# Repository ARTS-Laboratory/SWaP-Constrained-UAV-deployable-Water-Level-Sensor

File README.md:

# SWaP-Constrained UAV-deployable Water-Level Sensor (SCUWLS)
UAV Deployable Stage Height Sensor with Magnetic Docking Mechanism

This work is dicussed in two papers:
1. Md Asifuzzaman Khan, Muhammad Usman Khan, Amanda Sarka, P. G. Tien Tran, Michelle Eigbe, Austin R. J. Downey, Jason D. Bakos, Erick Blasche, and Jasim Imran. Energy budget analysis of swap-constrained uav-deployable water-level sensors with varying sampling intervals and idle currents. In SPIE Defense + Commercial Sensing 2026. SPIE, 2026
2. Corinne Smith, Joud Satme, Jacob Martin, Austin R.J. Downey, Nikolaos Vitzilaios, and Jasim Imran. UAV rapidly-deployable stage sensor with electro-permanent magnet docking mechanism for flood monitoring in undersampled watersheds. HardwareX, 12:e00325, oct 2022. doi:10.1016/j.ohx.2022.e00325.

## Hardware

<p align="center">
Figure 1: The "Georgetown Version 0.5" of the sensor, showing  (a) the assembled sensor package, and (b) a cross-section view of the sensor.
</p>

<p align="center">
Figure 2: Sensors deployed for continuous monitoring in the Charleston, SC area.
</p>

<p align="center">
Figure 3: Drone delivering a sensor package underneath a structure using Electro Parmanent Magnet docking mechanism.
</p>

## Versions 

### V0
1. Data logging saved onto SD card
2. Battery monitoring
3. Solar load sharing
4. Measures stage, temperature, pressure, humidity
5. EPM with wireless toggling to attach under structures

### V1 (projected)
1. Adaptive sampling algorithm
2. Wireless data transfer with GUI
3. Camera integration

## Licensing and Citation

[![CC BY-SA 4.0][cc-by-sa-shield]][cc-by-sa]

This work is licensed under a
[Creative Commons Attribution-ShareAlike 4.0 International License][cc-by-sa].

[cc-by-sa]: http://creativecommons.org/licenses/by-sa/4.0/
[cc-by-sa-image]: https://licensebuttons.net/l/by-sa/4.0/88x31.png
[cc-by-sa-shield]: https://img.shields.io/badge/License-CC%20BY--SA%204.0-lightgrey.svg

Cite as:

@Misc{ARTSLabUavDeployableStage,     
  author = {{ARTS-L}ab},  
  howpublished = {GitHub},  
  title  = {{SWaP-Constrained UAV-deployable Water-Level Sensor} (SCUWLS)},    
  groups = {{ARTS-L}ab},    
  url    = {https://github.com/ARTS-Laboratory/SWaP-Constrained-UAV-deployable-Water-Level-Sensor},   
}

<br>

<p align="center">
https://github.com/ARTS-Laboratory/UAV-Deployable-Stage-Height-Sensor
</p>

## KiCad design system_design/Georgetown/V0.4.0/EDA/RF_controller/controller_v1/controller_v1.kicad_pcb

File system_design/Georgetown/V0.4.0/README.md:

# UAV Rapidly-Deployable Stage Sensor with Electro-permanent Magnet Docking Mechanism for Flood Monitoring in Undersampled Watersheds

## bill of materials
A complete bill of materials, with specifications for the base package, solar add-on module, and EPM add-on module

## CAD
STL and F3D files of 3D printed parts 

## code
Calibration and data collection codes

## EDA
KiCAD schematics and PCB layouts of main and daughter boards

## figures
SVG and PDF files of all figures presented in the work

## testing_data
Data from benchtop and field tests

## data_headers.csv
Example data headers for csv file generated by data_collection.ino

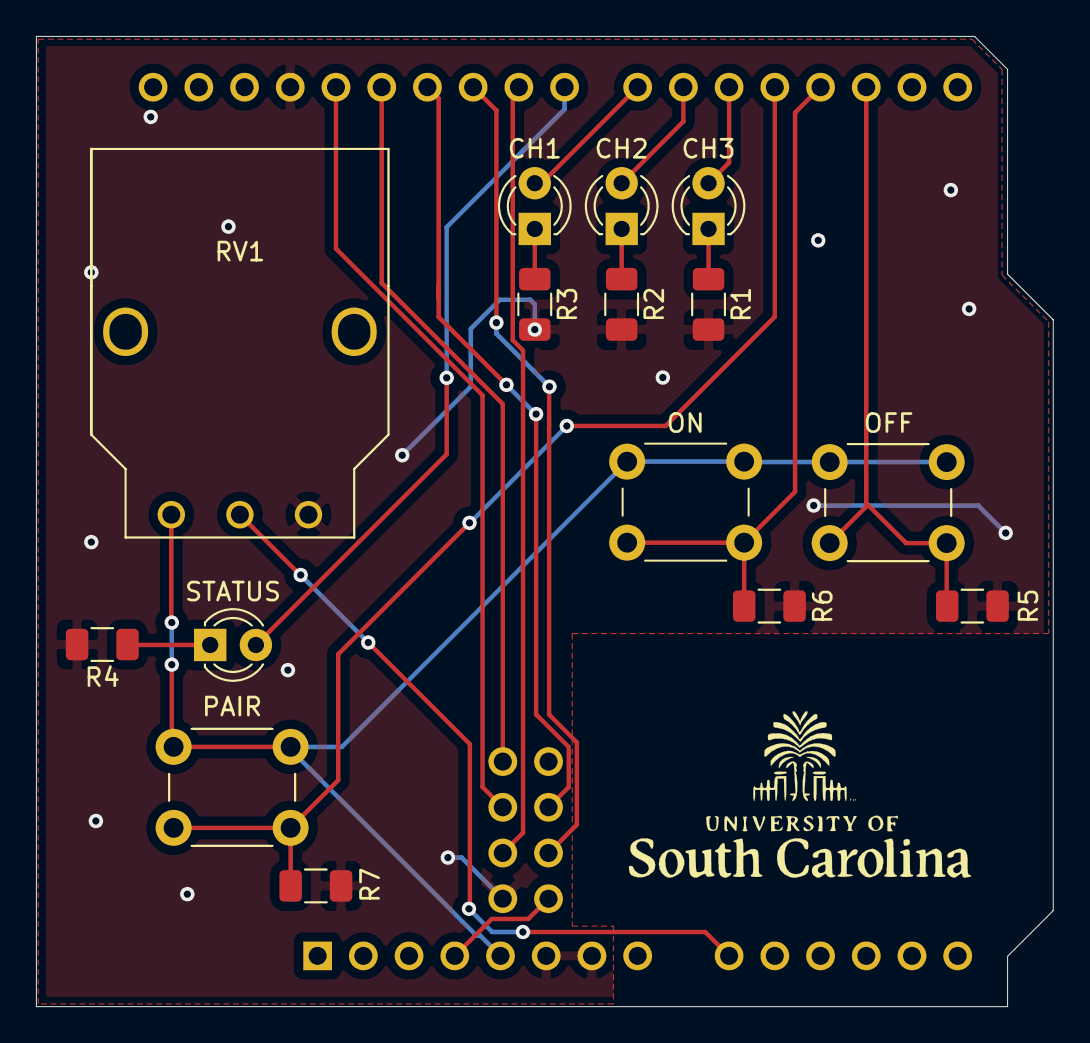
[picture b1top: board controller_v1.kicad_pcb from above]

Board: 2 copper layers, 56.5 x 53.9 mm, 17 parts (1 on the bottom side), 20 nets.

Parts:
A1: Arduino_UNO_R3
CH1, CH2, CH3: LED; LED_D3.0mm
OFF: SW_Push; SW_PUSH_6mm
ON: SW_Push; SW_PUSH_6mm
PAIR: SW_Push; SW_PUSH_6mm
R1, R2, R3, R4, R5, R6, R7: R; R_1206_3216Metric
RV1: R_POT; Bourns_PDB12
STATUS: LED; LED_D3.0mm
nRF24L01+: nRF24L01+

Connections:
GND: A1.6, A1.7, A1.29, R1.2, R2.2, R3.2, R4.2, R5.1, R6.2, R7.2, RV1.3, nRF24L01+.5
unnamed: A1.4, nRF24L01+.1
unnamed: A1.5, OFF.1, ON.1, PAIR.1, RV1.1
unnamed: A1.9, RV1.2
unnamed: A1.17, OFF.2, R5.2
unnamed: A1.18, ON.2, R6.1
unnamed: A1.19, PAIR.2, R7.1
unnamed: A1.20, CH3.2
unnamed: A1.21, CH2.2
unnamed: A1.22, CH1.2
unnamed: A1.23, STATUS.2
unnamed: A1.24, nRF24L01+.6
unnamed: A1.25, nRF24L01+.2
unnamed: A1.26, nRF24L01+.3
unnamed: A1.27, nRF24L01+.8
unnamed: A1.28, nRF24L01+.7
unnamed: CH3.1, R1.1
unnamed: CH2.1, R2.1
unnamed: CH1.1, R3.1
unnamed: R4.1, STATUS.1

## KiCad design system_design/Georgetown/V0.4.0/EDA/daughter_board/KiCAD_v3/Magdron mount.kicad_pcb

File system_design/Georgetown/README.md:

# Gerogetown
UAV deployable sensor package for measuring water height. 

## V0.1
1. Oldest version
2. Basic datalogger setup with modular RTC and SD card
3. Accelerometer integrated into daughter board

## V0.2
1. Teensy 4.0 microcontroller
2. Added environmental sensor

## V0.3
1. Teensy 4.0 or Arduino Nano microcontroller
2. Added DC current sensor

## V0.4
1. Arduino Nano microcontroller
2. Magnet power control circuit on daughter board
3. No accelerometer on daughter board
4. Solar panel load sharing on daughter board

## V0.5
1. Arduino Nano microcontroller
2. Uses dynamic sleep interval depending on battery voltage level
3. Uses permanent magnet to attach to steel structures
4. Easy sliding water-proof clear tube

## V0.6 (Proposed)
### Power electronics upgrade from V0.5
1.  Back to being UAV deployable using [this system](https://github.com/ARTS-Laboratory/UAV-Understructure-Sensor-Deployment-and-Recovery-System).
2.  Uses [buck converter](https://www.mouser.com/ProductDetail/Texas-Instruments/TPSM84203EAB?qs=EU6FO9ffTwdvD6IyQBtt5A%3D%3D&mgh=1&utm_id=22370133501&utm_source=google&utm_medium=cpc&utm_marketing_tactic=amercorp&gad_source=1&gad_campaignid=22380187564&gbraid=0AAAAADn_wf2gWZzSurQARsbyVMmz_4UDQ&gclid=Cj0KCQjw4qHEBhCDARIsALYKFNO-ZgKxWQY3H1w5GanZ_Tstxw3fUVWm0au9QuEBnVr6LlNByRsZf7YaAo9nEALw_wcB) instead of linear voltage regulator
3. Uses module that has [single ultra sound transducer](https://cdn.shopify.com/s/files/1/0550/8091/0899/files/11832.pdf?v=1726578772) to lower current consumption.

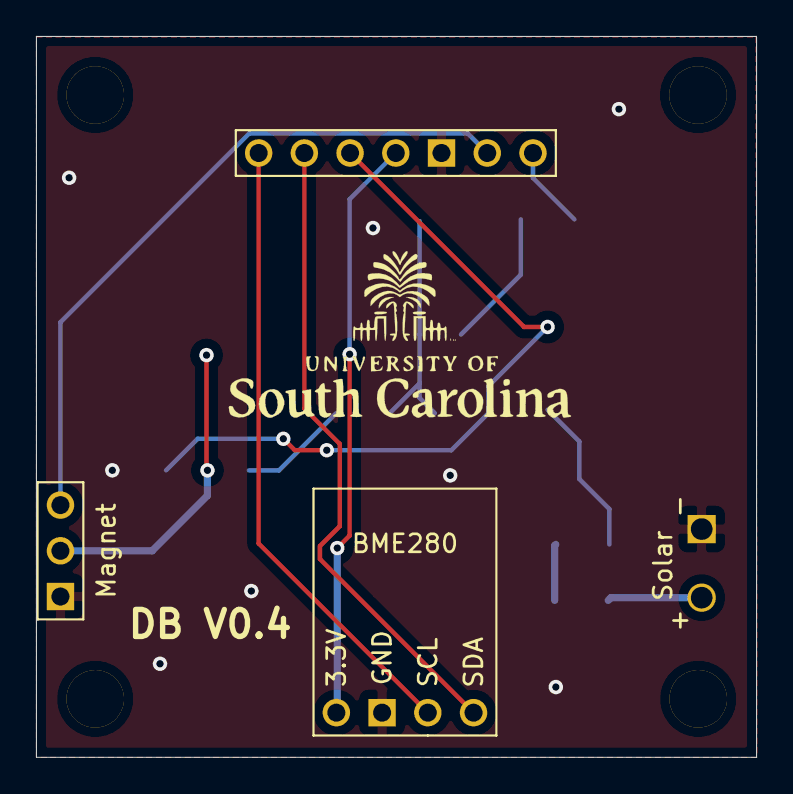
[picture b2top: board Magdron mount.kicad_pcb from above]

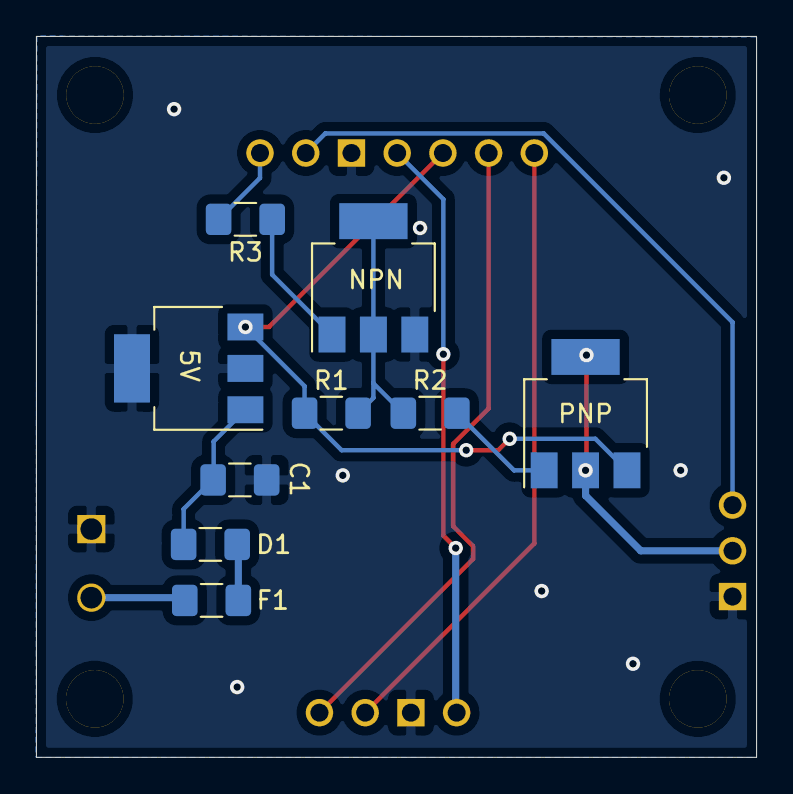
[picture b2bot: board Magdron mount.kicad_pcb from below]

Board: 2 copper layers, 40.0 x 40.0 mm, 18 parts (10 on the bottom side), 14 nets.

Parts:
5V: KA78M05_TO252; SOT-223-3_TabPin2
.: .; uofsc_logo_0_75in
.#2, .#3, .#4, .#5: MountingHole_3.2mm_M3_DIN965_Pad
BME280: BME280
C1: C; R_1206_3216Metric_Pad1.42x1.75mm_HandSolder
D1: D; R_1206_3216Metric_Pad1.42x1.75mm_HandSolder
F1: Fuse; R_1206_3216Metric_Pad1.42x1.75mm_HandSolder
Magnet: MAG-MAG; Magnet
NPN: BCP56; SOT-223-3_TabPin2
PNP: BCP51; SOT-223-3_TabPin2
R1: 1k; R_1206_3216Metric_Pad1.42x1.75mm_HandSolder
R2, R3: 100; R_1206_3216Metric_Pad1.42x1.75mm_HandSolder
Solar: power_input; XT60PW
U4: top_rail_v2

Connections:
GND: 5V.2, BME280.2, C1.1, Magnet.1, NPN.3, Solar.1, U4.6
unnamed: Magnet.2, PNP.2
unnamed: Magnet.3, U4.7
unnamed: 5V.1, C1.2, D1.1
unnamed: D1.2, F1.1
unnamed: F1.2, Solar.2
unnamed: PNP.1, R2.1
unnamed: 5V.3, PNP.3, R1.1, U4.4
unnamed: NPN.1, R3.1
unnamed: NPN.2, R1.2, R2.2
unnamed: R3.2, U4.8
unnamed: BME280.1, U4.5
unnamed: BME280.3, U4.2
unnamed: BME280.4, U4.3

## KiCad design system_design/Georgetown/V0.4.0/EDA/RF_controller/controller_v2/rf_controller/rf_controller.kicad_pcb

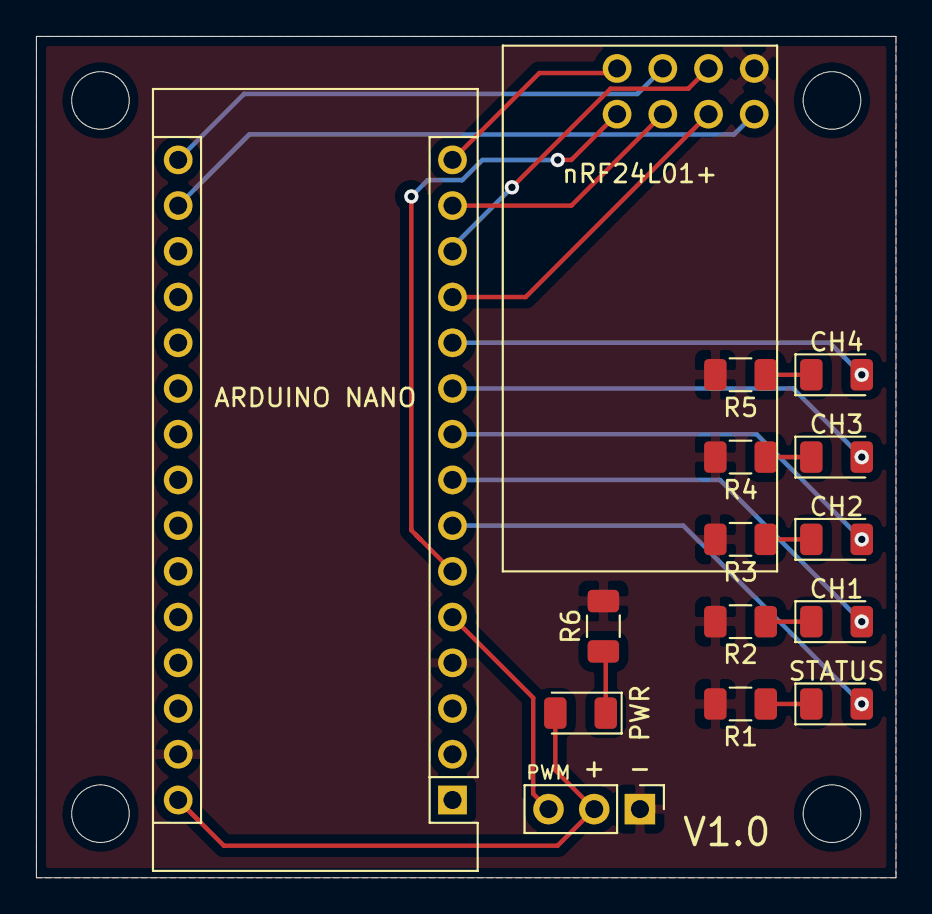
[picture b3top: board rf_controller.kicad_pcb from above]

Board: 2 copper layers, 47.8 x 46.7 mm, 15 parts (1 on the bottom side), 21 nets.

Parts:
ARDUINO NANO: Arduino_Nano_v2.x; Arduino_Nano
CH1, CH2, CH3, CH4: LED; LED_1206_3216Metric
PWM: Conn_01x03_Male; PinHeader_1x03_P2.54mm_Vertical
PWR: LED; LED_1206_3216Metric
R1, R2, R3, R4, R5, R6: R; R_1206_3216Metric
STATUS: LED; LED_1206_3216Metric
nRF24L01+: nRF24L01+

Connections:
GND: ARDUINO NANO.4, ARDUINO NANO.29, PWM.1, R1.2, R2.2, R3.2, R4.2, R5.2, R6.2, nRF24L01+.5
unnamed: ARDUINO NANO.5, PWM.3
unnamed: ARDUINO NANO.6, nRF24L01+.4
unnamed: ARDUINO NANO.7, STATUS.2
unnamed: ARDUINO NANO.8, CH1.2
unnamed: ARDUINO NANO.9, CH2.2
unnamed: ARDUINO NANO.10, CH3.2
unnamed: ARDUINO NANO.11, CH4.2
unnamed: ARDUINO NANO.12, nRF24L01+.2
unnamed: ARDUINO NANO.13, nRF24L01+.6
unnamed: ARDUINO NANO.14, nRF24L01+.3
unnamed: ARDUINO NANO.15, nRF24L01+.8
unnamed: ARDUINO NANO.16, nRF24L01+.7
unnamed: ARDUINO NANO.17, nRF24L01+.1
unnamed: ARDUINO NANO.30, PWM.2, PWR.2
unnamed: R1.1, STATUS.1
unnamed: CH1.1, R2.1
unnamed: CH2.1, R3.1
unnamed: CH3.1, R4.1
unnamed: CH4.1, R5.1
unnamed: PWR.1, R6.1

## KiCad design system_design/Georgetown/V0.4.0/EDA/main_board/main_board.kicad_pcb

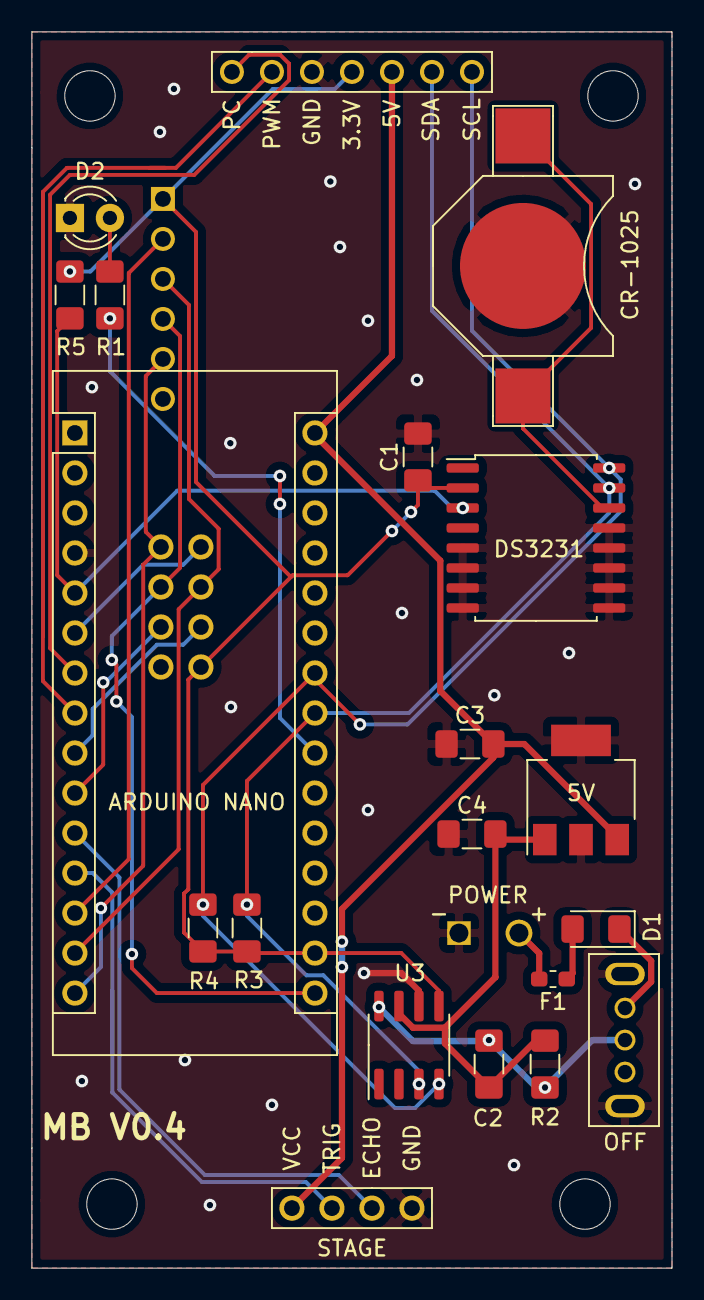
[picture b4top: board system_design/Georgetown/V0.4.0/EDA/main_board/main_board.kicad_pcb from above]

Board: 2 copper layers, 40.6 x 78.5 mm, 23 parts (0 on the bottom side), 25 nets.

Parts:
5V: KA78M05_TO252; SOT-223-3_TabPin2
ARDUINO NANO: Arduino_Nano_v2.x-MCU_Module; Arduino_Nano
C1, C2, C3, C4: C; C_1206_3216Metric_Pad1.42x1.75mm_HandSolder
CR-1025: Battery_Cell; battery_holder_10mm
D1: D; D_1206_3216Metric_Pad1.42x1.75mm_HandSolder
D2: LED; LED_D3.0mm
DS3231: DS3231M; SOIC-16W_7.5x10.3mm_P1.27mm
F1: Fuse; R_0603_1608Metric_Pad1.05x0.95mm_HandSolder
MICRO SD: small_microSD; small_microSD_v2
POWER: XP60PW; XT60PW
R1: 1k; C_1206_3216Metric_Pad1.42x1.75mm_HandSolder
R2: Rs; R_1206_3216Metric_Pad1.42x1.75mm_HandSolder
R3, R4: 4.7k; C_1206_3216Metric_Pad1.42x1.75mm_HandSolder
R5: 4.7k; R_1206_3216Metric_Pad1.42x1.75mm_HandSolder
STAGE: HCSR04
U1: top_rail_v2
U3: INA219AxD; SOIC-8_3.9x4.9mm_P1.27mm
nRF24L01+1: nRF24L01+
switch1: grounded_switch

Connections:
GND: 5V.2, ARDUINO NANO.4, ARDUINO NANO.29, C1.2, C3.1, C4.1, CR-1025.2, D2.1, DS3231.5, DS3231.6, DS3231.7, DS3231.8, DS3231.9, DS3231.10, DS3231.11, DS3231.12, DS3231.13, MICRO SD.6, POWER.1, STAGE.1, U1.6, U3.6, nRF24L01+1.5, switch1.4, switch1.5
unnamed: ARDUINO NANO.5, DS3231.3, R5.1
unnamed: ARDUINO NANO.6, nRF24L01+1.4
unnamed: ARDUINO NANO.7, U1.8
unnamed: ARDUINO NANO.8, U1.7
unnamed: ARDUINO NANO.9, nRF24L01+1.2
unnamed: ARDUINO NANO.10, nRF24L01+1.6
unnamed: ARDUINO NANO.11, STAGE.2
unnamed: ARDUINO NANO.12, STAGE.3
unnamed: ARDUINO NANO.13, MICRO SD.2
unnamed: ARDUINO NANO.14, MICRO SD.3, nRF24L01+1.3
unnamed: ARDUINO NANO.15, MICRO SD.5, nRF24L01+1.8
unnamed: ARDUINO NANO.16, MICRO SD.4, nRF24L01+1.7
unnamed: ARDUINO NANO.17, C1.1, DS3231.2, MICRO SD.1, R3.1, R4.1, R5.2, U1.5, U3.5, nRF24L01+1.1
unnamed: ARDUINO NANO.22, R1.1
unnamed: ARDUINO NANO.23, DS3231.15, R3.2, U1.3, U3.3
unnamed: ARDUINO NANO.24, DS3231.16, R4.2, U1.2, U3.4
unnamed: 5V.3, ARDUINO NANO.30, C3.2, STAGE.4, U1.4
unnamed: CR-1025.1, DS3231.14
unnamed: C2.1, R2.1, U3.8, switch1.2
unnamed: 5V.1, C2.2, C4.2, R2.2, U3.7
unnamed: D1.1, switch1.1
unnamed: D1.2, F1.1
unnamed: D2.2, R1.2
unnamed: F1.2, POWER.2

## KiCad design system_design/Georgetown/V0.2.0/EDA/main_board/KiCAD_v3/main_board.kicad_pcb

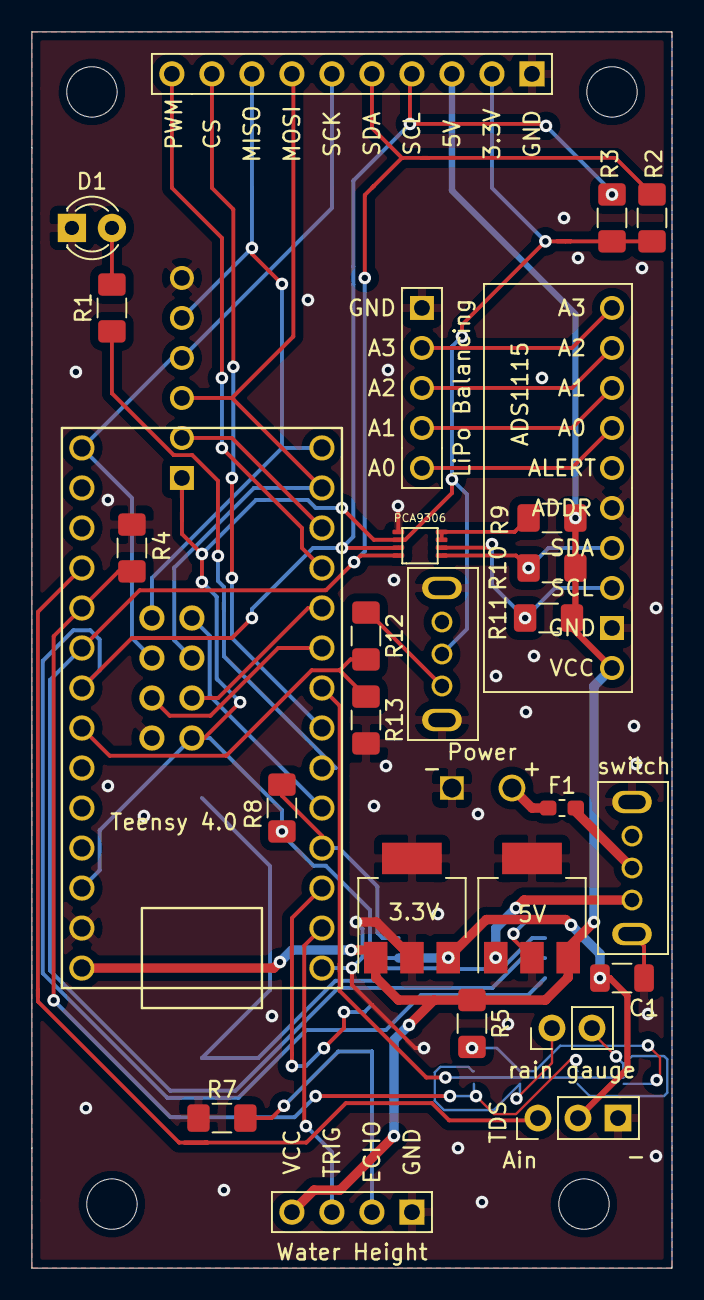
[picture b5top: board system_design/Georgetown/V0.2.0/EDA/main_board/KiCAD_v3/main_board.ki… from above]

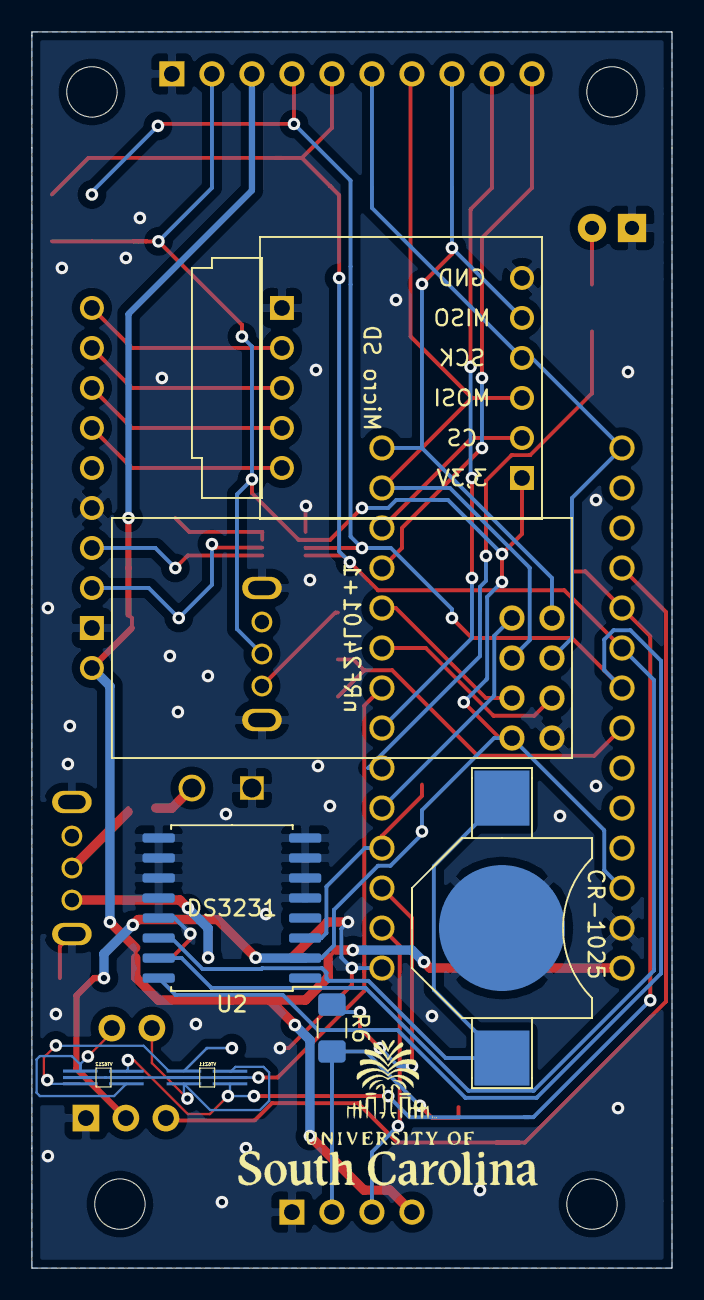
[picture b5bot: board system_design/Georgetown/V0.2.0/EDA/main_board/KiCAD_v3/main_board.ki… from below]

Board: 2 copper layers, 40.6 x 78.5 mm, 35 parts (3 on the bottom side), 39 nets.

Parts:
3.3V, 5V: KA78M05_TO252; SOT-223-3_TabPin2
ADS1115: ADS1115
C1: C; R_1206_3216Metric
CR-1025: Battery_Cell; battery_holder_10mm
D1: LED; LED_D3.0mm
F1: Fuse; R_0603_1608Metric_Pad1.05x0.95mm_HandSolder
LiPo Balancing: ADS_Conn
Micro SD: small_microSD
PCA9306: PCA9306
Power: XP60PW; XT60PW
R1, R12: 1k; R_1206_3216Metric_Pad1.42x1.75mm_HandSolder
R2, R3, R8, R10, R11: 4.7k; R_1206_3216Metric_Pad1.42x1.75mm_HandSolder
R4, R5: R; R_1206_3216Metric_Pad1.42x1.75mm_HandSolder
R6: 4.4k; R_1206_3216Metric_Pad1.42x1.75mm_HandSolder
R7: 4.1k; R_1206_3216Metric_Pad1.42x1.75mm_HandSolder
R9: 200; R_1206_3216Metric_Pad1.42x1.75mm_HandSolder
R13: 10k; R_1206_3216Metric_Pad1.42x1.75mm_HandSolder
TDS: tds_3pin; PinHeader_1x03_P2.54mm_Vertical
Teensy 4.0: Teensy4.0; teensy4.0
U2: DS3231M; SOIC-16W_7.5x10.3mm_P1.27mm
VT6Z11, VT6Z12: VT6Z1
Water Height: HCSR04
nRF24L01+1: nRF24L01+
rain gauge: rg_2pin; PinHeader_1x02_P2.54mm_Vertical
switch: grounded_switch
switch2: grounded_switch-whs5-rescue; grounded_switch
top_rail1: top_rail

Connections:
GND: 3.3V.2, 5V.2, ADS1115.6, ADS1115.9, C1.2, CR-1025.2, D1.1, LiPo Balancing.1, Micro SD.6, PCA9306.1, Power.1, R4.2, R7.1, R13.2, TDS.3, Teensy 4.0.1, Teensy 4.0.32, U2.5, U2.6, U2.7, U2.8, U2.9, U2.10, U2.11, U2.12, U2.13, Water Height.1, nRF24L01+1.5, switch.4, switch.5, switch2.4, switch2.5, top_rail1.9
unnamed: CR-1025.1, U2.14
unnamed: 3.3V.3, C1.1, Micro SD.1, PCA9306.2, R2.1, R3.1, R8.1, TDS.2, Teensy 4.0.31, U2.2, nRF24L01+1.1, switch2.2, top_rail1.8
unnamed: D1.2, R1.2
unnamed: F1.1, Power.2
unnamed: F1.2, switch.2
unnamed: Micro SD.2, Teensy 4.0.12
unnamed: Micro SD.3, Teensy 4.0.13, nRF24L01+1.3, top_rail1.3
unnamed: Micro SD.4, Teensy 4.0.20, nRF24L01+1.7, top_rail1.4
unnamed: Micro SD.5, Teensy 4.0.14, nRF24L01+1.8, top_rail1.2
unnamed: R1.1, Teensy 4.0.6
unnamed: PCA9306.4, R2.2, Teensy 4.0.25, U2.15, top_rail1.5
unnamed: PCA9306.3, R3.2, Teensy 4.0.26, U2.16, top_rail1.6
unnamed: R4.1, Teensy 4.0.24, VT6Z11.4, VT6Z12.6
unnamed: R5.2, VT6Z11.1, VT6Z12.3
unnamed: R6.1, Teensy 4.0.3
unnamed: R6.2, R7.2, Water Height.2
unnamed: R8.2, Teensy 4.0.4, U2.3
unnamed: PCA9306.7, PCA9306.8, R9.2
unnamed: ADS1115.7, PCA9306.5, R10.1
unnamed: 3.3V.1, 5V.3, ADS1115.10, R5.1, R9.1, R10.2, R11.2, Teensy 4.0.33, Water Height.4, top_rail1.7
unnamed: ADS1115.8, PCA9306.6, R11.1
unnamed: R12.1, switch2.1
unnamed: R12.2, R13.1, Teensy 4.0.27
unnamed: TDS.1, Teensy 4.0.23
unnamed: Teensy 4.0.2, Water Height.3
unnamed: Teensy 4.0.5, nRF24L01+1.4
unnamed: Teensy 4.0.7, top_rail1.1
unnamed: Teensy 4.0.8, VT6Z11.2, VT6Z11.5, VT6Z12.2, VT6Z12.5
unnamed: Teensy 4.0.9, nRF24L01+1.6
unnamed: Teensy 4.0.10, nRF24L01+1.2
unnamed: Teensy 4.0.11, top_rail1.10
unnamed: ADS1115.1, LiPo Balancing.2
unnamed: ADS1115.2, LiPo Balancing.3
unnamed: ADS1115.3, LiPo Balancing.4
unnamed: ADS1115.4, LiPo Balancing.5
unnamed: 5V.1, switch.1
unnamed: VT6Z11.3, VT6Z11.6, rain gauge.1
unnamed: VT6Z12.1, VT6Z12.4, rain gauge.2

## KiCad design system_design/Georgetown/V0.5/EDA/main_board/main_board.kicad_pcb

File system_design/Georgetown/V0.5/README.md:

# UAV Rapidly-Deployable Stage Sensor with Permanent Magnet Docking Mechanism for Flood Monitoring in Undersampled Watersheds
## Deployment note
* Do not plug or unplug the SD card while power is on. Swtich must be turned to the off position to plug/unplug the SD card. 
## Fully assembled sensor package

## V0.5 PCB Top side

## V0.5 PCB Bottom side

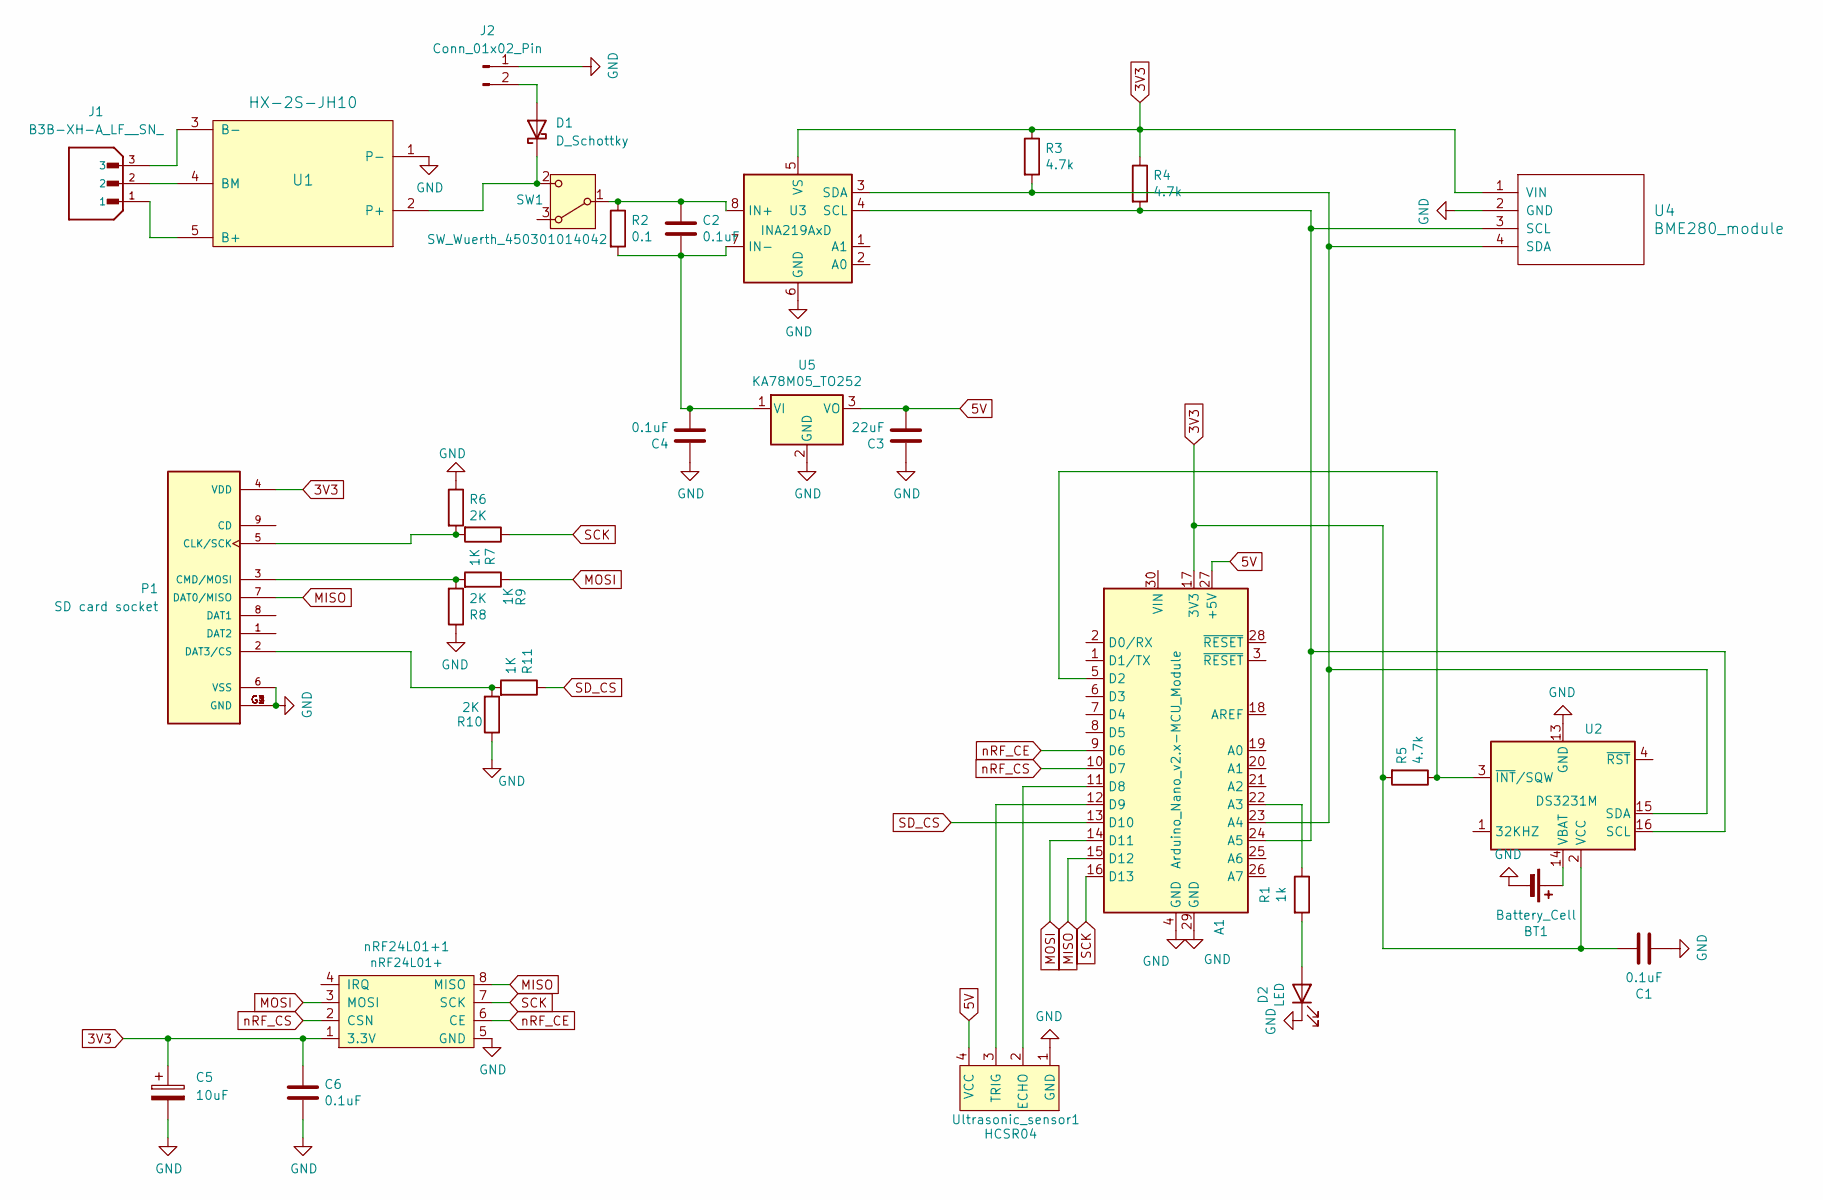
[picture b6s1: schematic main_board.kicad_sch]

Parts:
A1: Arduino_Nano_v2.x-MCU_Module; Arduino_Nano
BT1: Battery_Cell; battery_holder_10mm
C1, C2, C4: 0.1uF; C_1206_3216Metric_Pad1.42x1.75mm_HandSolder
C3: 22uF; C_1206_3216Metric_Pad1.42x1.75mm_HandSolder
C5: 10uF; CP_Radial_D4.0mm_P2.00mm
C6: 0.1uF; C_1206_3216Metric_Pad1.33x1.80mm_HandSolder
D1: D_Schottky; D_1206_3216Metric
D2: LED; LED_D3.0mm
J1: B3B-XH-A_LF__SN_; XH2.54; PARTREV 7/4/21
J2: Conn_01x02_Pin; PinHeader_1x02_P2.54mm_Vertical
P1: SD card socket; SUNTECH_ST-TF-003A
R1: 1k; C_1206_3216Metric_Pad1.42x1.75mm_HandSolder
R2: 0.1; R_1206_3216Metric_Pad1.42x1.75mm_HandSolder
R3, R4: 4.7k; C_1206_3216Metric_Pad1.42x1.75mm_HandSolder
R5: 4.7k; R_1206_3216Metric_Pad1.42x1.75mm_HandSolder
R6, R8, R10: 2K; C_1206_3216Metric_Pad1.33x1.80mm_HandSolder
R7, R9, R11: 1K; C_1206_3216Metric_Pad1.33x1.80mm_HandSolder
SW1: SW_Wuerth_450301014042; SW_Slide-03_Wuerth-WS-SLTV_10x2.5x6.4_P2.54mm
U1: HX-2S-JH10
U2: DS3231M; SOIC-16W_7.5x10.3mm_P1.27mm
U3: INA219AxD; SOIC-8_3.9x4.9mm_P1.27mm
U4: BME280_module
U5: KA78M05_TO252; SOT-223-3_TabPin2
Ultrasonic_sensor1: HCSR04
nRF24L01+1: nRF24L01+

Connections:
3V3: A1.17 (3V3), C1.1, C5.1, C6.1, P1.4 (VDD), R3.1, R4.1, R5.2, U2.2 (VCC), U3.5 (VS), U4.1 (VIN), nRF24L01+1.1 (3.3V)
5V: A1.27 (+5V), C3.2, U5.3 (VO), Ultrasonic_sensor1.4 (VCC)
GND: A1.4 (GND), A1.29 (GND), BT1.2 (-), C1.2, C3.1, C4.1, C5.2, C6.2, D2.1 (K), J2.1, P1.6 (VSS), P1.G1 (GND), P1.G2 (GND), P1.G3 (GND), P1.G4 (GND), R6.1, R8.1, R10.1, U1.1 (P-), U2.5 (GND), U2.6 (GND), U2.7 (GND), U2.8 (GND), U2.9 (GND), U2.10 (GND), U2.11 (GND), U2.12 (GND), U2.13 (GND), U3.6 (GND), U4.2 (GND), U5.2 (GND), Ultrasonic_sensor1.1 (GND), nRF24L01+1.5 (GND)
MISO: A1.15 (D12), P1.7 (DAT0/MISO), nRF24L01+1.8 (MISO)
MOSI: A1.14 (D11), R9.1, nRF24L01+1.3 (MOSI)
unnamed: A1.22 (A3), R1.1
unnamed: A1.23 (A4), R3.2, U2.15 (SDA), U3.3 (SDA), U4.4 (SDA)
unnamed: A1.24 (A5), R4.2, U2.16 (SCL), U3.4 (SCL), U4.3 (SCL)
unnamed: A1.5 (D2), R5.1, U2.3 (~INT/SQW)
unnamed: A1.11 (D8), Ultrasonic_sensor1.2 (ECHO)
unnamed: A1.12 (D9), Ultrasonic_sensor1.3 (TRIG)
unnamed: BT1.1 (+), U2.14 (VBAT)
unnamed: D1.2 (A), J2.2
unnamed: D1.1 (K), SW1.2 (C), U1.2 (P+)
unnamed: D2.2 (A), R1.2
unnamed: P1.5 (CLK/SCK), R6.2, R7.2
unnamed: P1.3 (CMD/MOSI), R8.2, R9.2
unnamed: P1.2 (DAT3/CS), R10.2, R11.2
unnamed: C2.1, R2.1, SW1.1 (B), U3.8 (IN+)
unnamed: J1.1, U1.5 (B+)
unnamed: J1.3, U1.3 (B-)
unnamed: J1.2, U1.4 (BM)
unnamed: C2.2, C4.2, R2.2, U3.7 (IN-), U5.1 (VI)
SCK: A1.16 (D13), R7.1, nRF24L01+1.7 (SCK)
SD_CS: A1.13 (D10), R11.1
nRF_CE: A1.9 (D6), nRF24L01+1.6 (CE)
nRF_CS: A1.10 (D7), nRF24L01+1.2 (CSN)

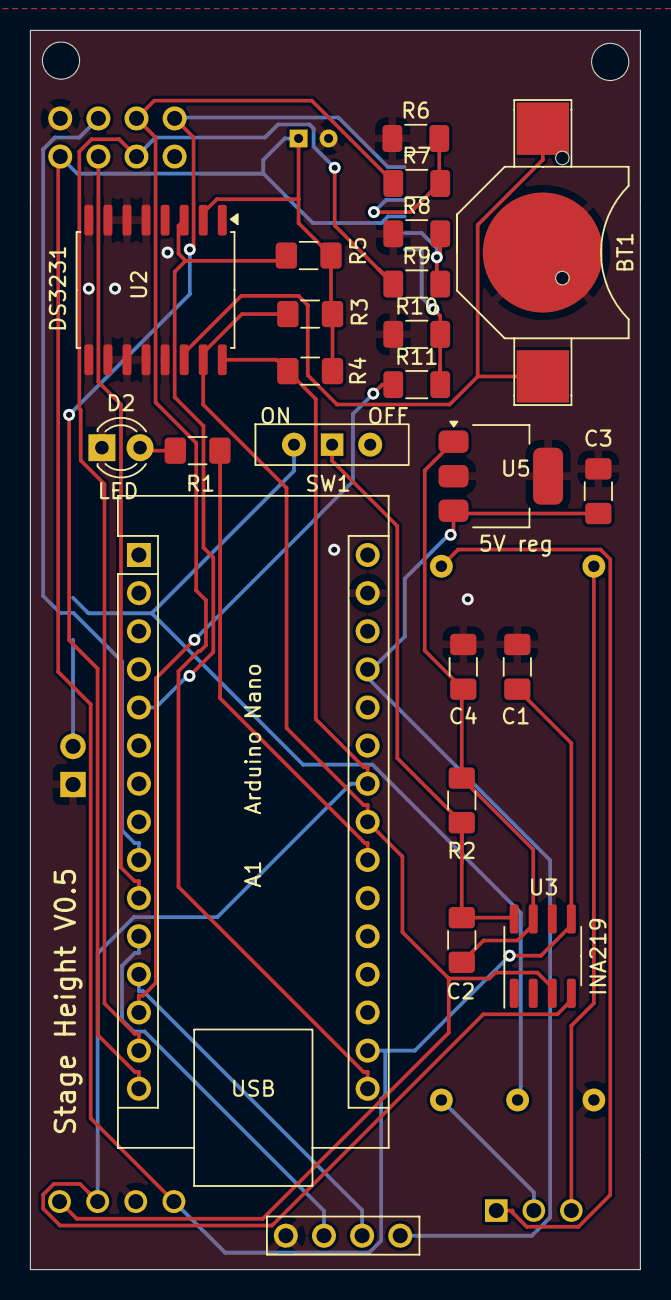
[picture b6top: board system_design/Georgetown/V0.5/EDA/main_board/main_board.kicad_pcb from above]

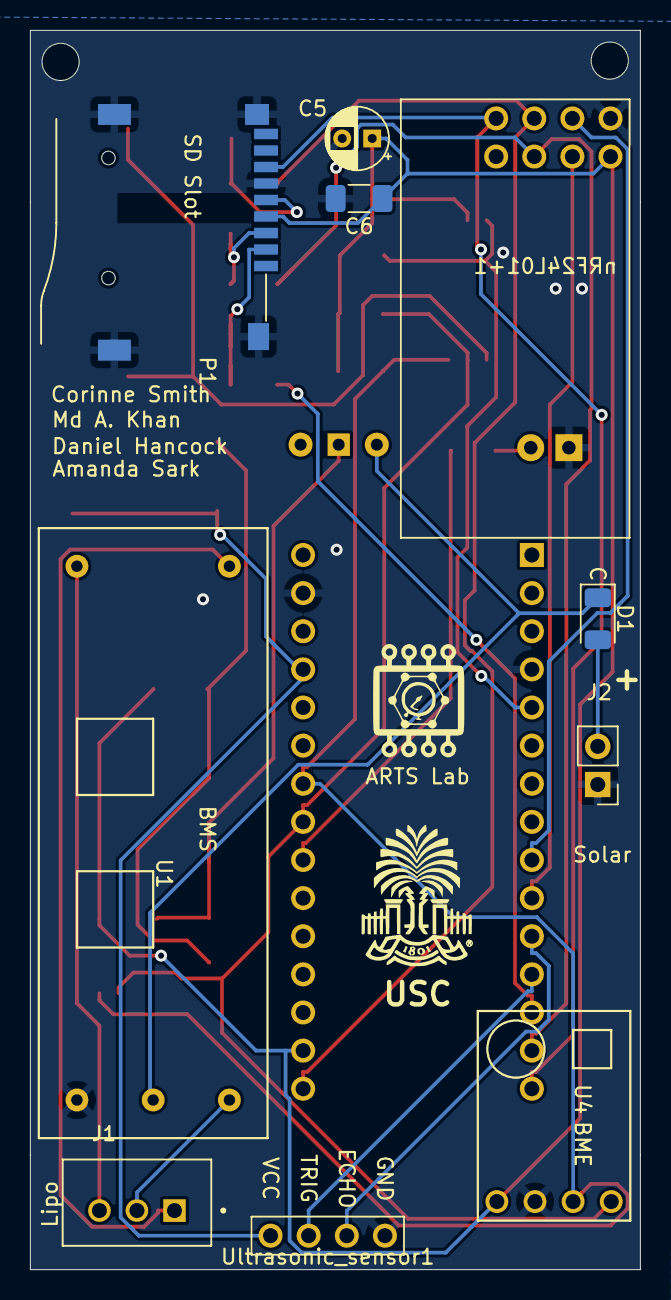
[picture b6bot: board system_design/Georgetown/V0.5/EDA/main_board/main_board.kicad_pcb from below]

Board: 2 copper layers, 40.6 x 82.6 mm, 34 parts (11 on the bottom side), 27 nets.

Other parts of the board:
ARTS Lab: LOGO
USC: UofSC; LOGO

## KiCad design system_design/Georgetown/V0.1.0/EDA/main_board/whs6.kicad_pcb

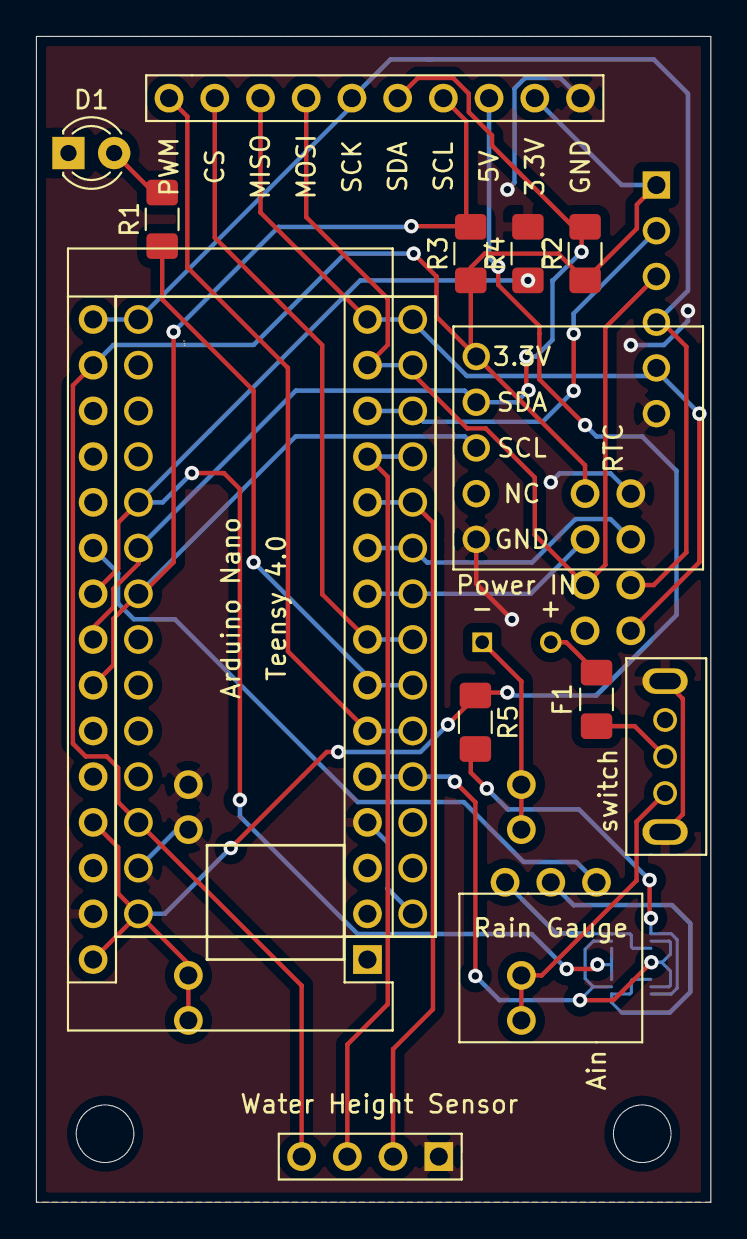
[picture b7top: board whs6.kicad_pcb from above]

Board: 2 copper layers, 37.5 x 64.8 mm, 20 parts (0 on the bottom side), 27 nets.

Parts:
Arduino Nano: Arduino_Nano_v2.x; Arduino_Nano
D1: LED; LED_D3.0mm
F1: Fuse; R_1206_3216Metric_Pad1.42x1.75mm_HandSolder
MP1584: MP1584; MP1584_back
Micro SD: small_microSD
Power IN: XP60PW; XT60PW
R1: 1k; R_1206_3216Metric_Pad1.42x1.75mm_HandSolder
R2, R3: 4.7k; R_1206_3216Metric_Pad1.42x1.75mm_HandSolder
R4, R5: R; R_1206_3216Metric_Pad1.42x1.75mm_HandSolder
RTC: small_DS3231
Rain Gauge: rain_gauge-whs5-rescue; Rainfall_sensor
Teensy 4.0: Teensy4.0; teensy4.0
Ultrasonic_sensor1: HCSR04
VT6Z11, VT6Z12: VT6Z1
nRF24L01+: nRF24L01+
switch: grounded_switch
top_rail1: top_rail

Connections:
GND: Arduino Nano.4, Arduino Nano.29, D1.1, MP1584.7, MP1584.8, Micro SD.6, R4.2, RTC.1, Teensy 4.0.1, Teensy 4.0.32, Ultrasonic_sensor1.1, nRF24L01+.5, switch.4, switch.5, top_rail1.9
unnamed: Arduino Nano.5, Teensy 4.0.4, VT6Z11.2, VT6Z11.5, VT6Z12.2, VT6Z12.5
unnamed: Arduino Nano.6, Teensy 4.0.5, top_rail1.10
unnamed: Arduino Nano.7, R1.1, Teensy 4.0.6
unnamed: Arduino Nano.8, Teensy 4.0.7, top_rail1.1
unnamed: Arduino Nano.9, Teensy 4.0.8, nRF24L01+.2
unnamed: Arduino Nano.10, Teensy 4.0.9, nRF24L01+.6
unnamed: Arduino Nano.11, Teensy 4.0.10, Ultrasonic_sensor1.2
unnamed: Arduino Nano.12, Teensy 4.0.11, Ultrasonic_sensor1.3
unnamed: Arduino Nano.13, Micro SD.2, Teensy 4.0.12
unnamed: Arduino Nano.14, Micro SD.3, Teensy 4.0.13, nRF24L01+.3, top_rail1.3
unnamed: Arduino Nano.15, Micro SD.5, Teensy 4.0.14, nRF24L01+.8, top_rail1.2
unnamed: Arduino Nano.16, Micro SD.4, Teensy 4.0.20, nRF24L01+.7, top_rail1.4
unnamed: Arduino Nano.17, Micro SD.1, R2.1, R3.1, RTC.5, Teensy 4.0.31, Ultrasonic_sensor1.4, nRF24L01+.1, top_rail1.8
unnamed: Arduino Nano.21, Rain Gauge.3
unnamed: Arduino Nano.22, R4.1, Teensy 4.0.24, VT6Z11.4, VT6Z12.6
unnamed: Arduino Nano.23, R2.2, RTC.4, Teensy 4.0.25, top_rail1.5
unnamed: Arduino Nano.24, R3.2, RTC.3, Teensy 4.0.26, top_rail1.6
unnamed: Arduino Nano.27, Arduino Nano.30, MP1584.5, MP1584.6, R5.1, Teensy 4.0.33, top_rail1.7
unnamed: D1.2, R1.2
unnamed: F1.1, Power IN.2
unnamed: F1.2, switch.2
unnamed: MP1584.3, MP1584.4, Power IN.1
unnamed: R5.2, VT6Z11.1, VT6Z12.3
unnamed: MP1584.1, MP1584.2, switch.1
unnamed: Rain Gauge.1, VT6Z11.3, VT6Z11.6
unnamed: Rain Gauge.2, VT6Z12.1, VT6Z12.4

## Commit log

2025-03-27 BOM Update
    Remove old, add new
    Excel has links
    LaTeX does not
2025-04-17 PCB modified
2025-04-17 QR code added
2025-04-24 CAD updated
2025-04-29 PCB design modified
2025-04-29 PCB design changed
2025-04-29 pcb CAD updated
2025-04-30 CAD changed
2025-04-30 pcb polished
2025-05-01 PCB settings changed
2025-05-01 BOM updated
2025-05-05 EDA cleaned up
2025-05-06 OS code bug fixed
2025-05-15 OS updated
2025-06-03 PCB updated
2025-06-03 read me updated
2025-06-04 PCB updated - cosmetics
2025-06-04 pcb images updated
2025-06-05 Diode added in BOM and CAD folder cleaned
2025-06-12 bom update
2025-06-12 PCB correction for v0.5
2025-06-13 gerbers generated
2025-07-01 updated gitignore
2025-07-01 updated BOM
2025-07-18 PCB and chassis design changed
2025-07-31 Test data added
2025-07-31 Dynamic smapler created
2025-08-04 OS update
2025-08-07 part name embossed
2025-08-13 part name embossed in chassis
2025-08-25 codeupdate
2025-08-25 logs added
2025-09-01 new logs added
2025-09-16 PCB tray design updated
2025-09-17 sticker label created
2025-09-17 moved sticker location
2025-10-02 CAD update ongoing
2025-10-13 O-ring updated
2025-10-15 Kicad version updated.
2025-10-15 Schematic PDF generated for ease of working
2025-10-15 Some memory optimization performed in code
2025-11-10 Some changes to hardware testing codes
2025-11-11 added 2025 pictures
2025-11-13 BOM and PCB designation updated
2025-11-13 test data deleted
2025-11-13 Image updated
2025-11-13 Fix image filename in README.md
    Corrected the image source filename in the README.
2025-11-13 Fix image filename in README.md
2025-11-13 Increase overview image size in README.md
    Updated image size for overview in README.
2025-11-19 Add system diagram to README.md
2025-12-05 test program updated
2025-12-10 removed zip file back up
2025-12-10 updated git ignore
2025-12-10 ADDED 0.5.1
2025-12-16 program updated
2026-01-02 SilkScreenUpdated
2026-01-14 PCB file changed
2026-01-14 Gerber files renamed
2026-01-28 New version 0.6 created
2026-01-28 Some relevant CAD added for 0.6
2026-02-23 CAD file added
2026-02-23 Folder changed
2026-04-30 Delete bill_of_materials.xlsx
    This was a duplicate and outdated, best I could tell
2026-05-29 V0.5.2 added
2026-06-01 PCB gerber created
2026-06-01 dDeletedlots of old kicad versions and files
2026-06-01 Folders organized
2026-06-01 BOM changed
2026-06-03 Folder organized
